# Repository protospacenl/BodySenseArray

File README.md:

# BodySenseArray
Body Sensor Array

## Data transfer
Data transfer between sensor units uses RS485. Use a RS485 to usb converter to send data over to the PC.

Serial settings:
 * Baudrate: 250000
 * 8n1
 * no flow control

## Sensor data format
Each packet starts with a `%` start token and ends with a CRC. Check the crc to verify data integrity. If crc is not valid the received packet should be discarded.

 * byte order: little endian
 * format: `%<id><temperature><acc_x><acc_y><acc_z><gyro_x><gyro_y><gyro_z><crc>`

field | type
--- | ---
% | uint8_t
id | uint8_t
temperature | uint16_t
acc_[xyz] | int16_t
gyro_[xyz] | int16_t
crc | uint8_t

## CRC
CRC algorithm used is the [Dalles iButton 8-bit CRC](https://www.microchip.com/webdoc/AVRLibcReferenceManual/group__util__crc_1ga37b2f691ebbd917e36e40b096f78d996.html).

Example C implementation  (taken from above link):
```C
uint8_t
_crc_ibutton_update(uint8_t crc, uint8_t data)
{
    uint8_t i;

    crc = crc ^ data;
    for (i = 0; i < 8; i++)
    {
        if (crc & 0x01)
            crc = (crc >> 1) ^ 0x8C;
        else
            crc >>= 1;
    }
    
    return crc;
}
```
or in python (see [examples](https://github.com/protospacenl/BodySenseArray/blob/90c5e3de4db39f0ca5cd2b3785d3c42a4cba6765/examples/serial_read/serial_read.py#L60) for usage)
```python
def compute_crc(data):
    crc = 0x00
    for c in data[:-1]:
        crc = crc ^ c
        for i in range(0, 8):
            if crc & 0x01:
                crc  = (crc >> 1) ^ 0x8c
            else:
                crc = crc >> 1
    return crc
```

## Conversions
For efficiency the sensor data is in its integer form and needs to be translated to real world values. 
See the [examples](https://github.com/protospacenl/BodySenseArray/tree/master/examples) for implementation details.

### Temperature
```python
def temperature_from_raw(t):
    return t * 0.00390625
```

### acceleration
Translation from the raw acceleration values to *g*:
`(float)in * 0.061 * (g >> 1) / 1000.0`  
where *in* is the raw 16-bit two's complement value and *g* is the sensitivity (currently 2).

Range for 2g:
 - min: -1.99848g
 - max: 1.99787g

Example:
```python
def acc_from_raw(in, g=2):
    return in * 0.061 * (g >> 1) / 1000.
 ```

### angular rate
Translation from the raw angular rate to *dps*:
`(float)in * 4.375 * (dps / 125) / 1000.0`
where *in* is the raw 16-bit two's complement value and *dps* is the sensitivity (currently 2000).

Range for 2000dps:
 - min: -2293.76 dps
 - max: 2293.69 dps

Example:
```python
def dps_from_raw(in, dps=2000):
  return in * 4.375 * (dps / 125) / 1000.
```

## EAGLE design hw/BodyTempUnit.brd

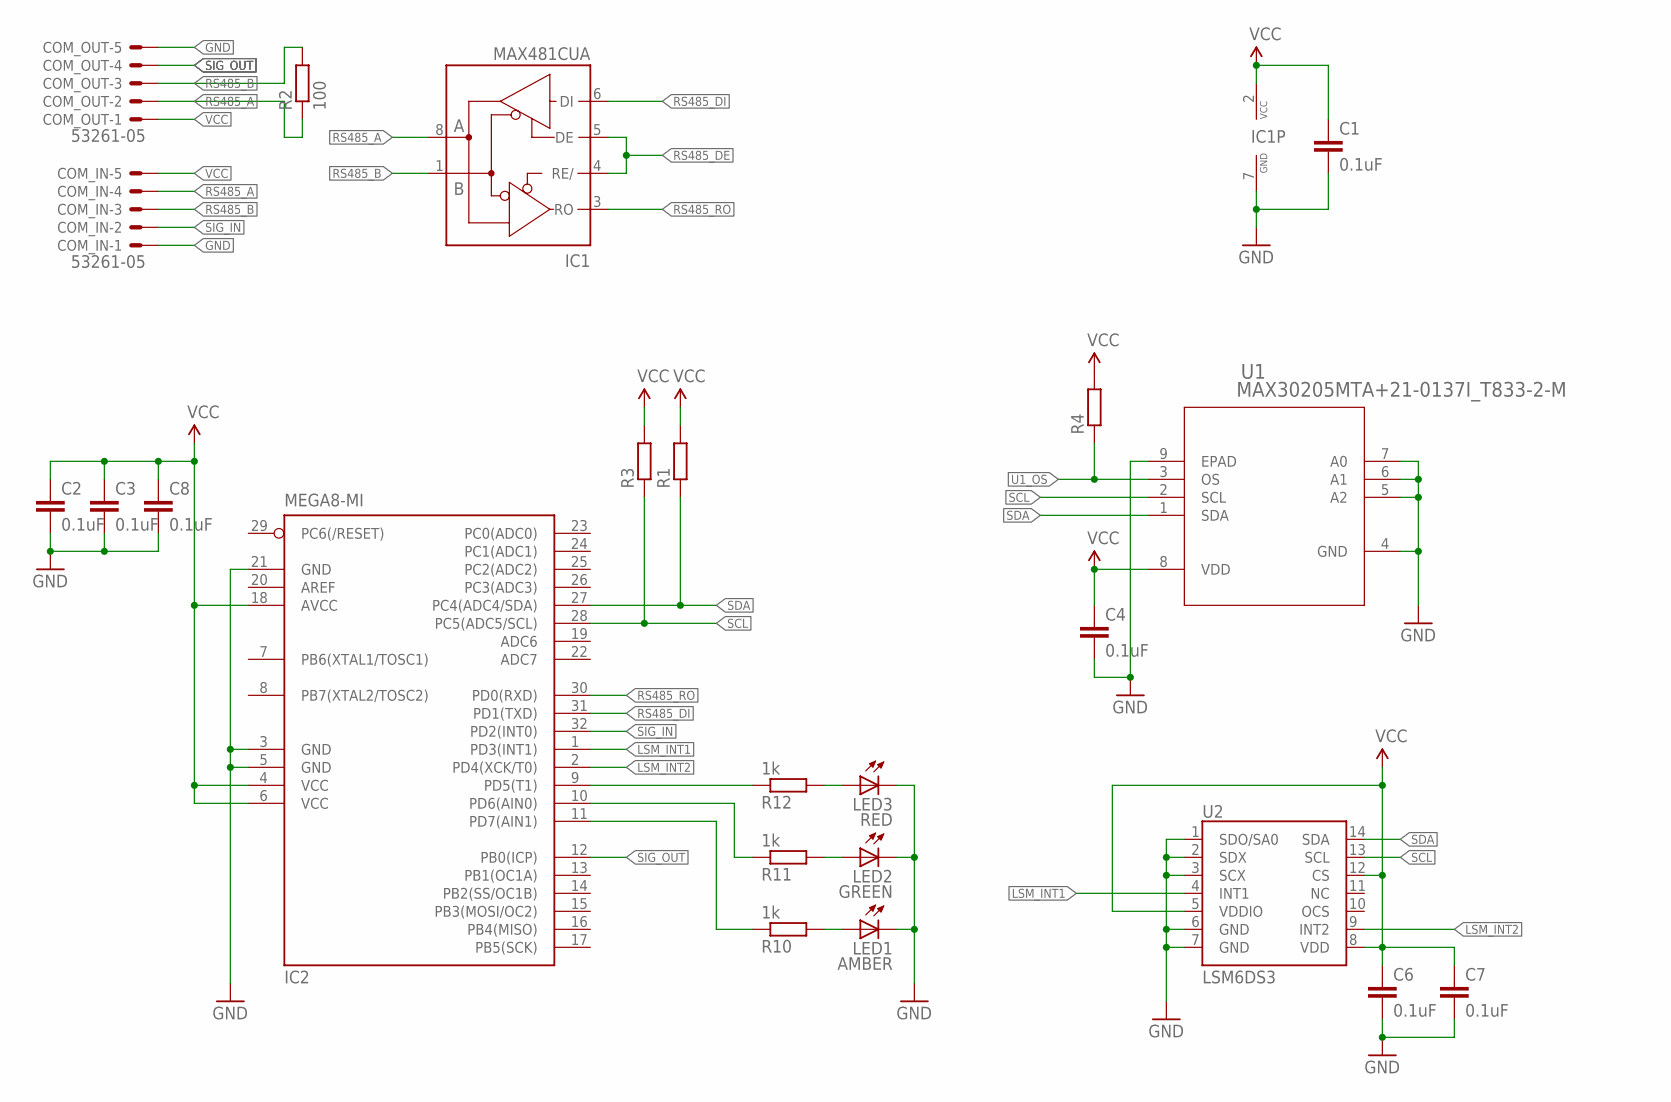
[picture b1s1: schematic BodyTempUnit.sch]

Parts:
C1, C2, C3, C4, C6, C7, C8: 0.1uF; C0603K
COM_IN: 53261-05
COM_OUT: 53261-05
IC1: MAX481CUA; UMAX8
IC2: MEGA8-MI; MLF32
LED1: AMBER; CHIPLED_0603
LED2: GREEN; CHIPLED_0603
LED3: RED; CHIPLED_0603
R1, R3, R4: R-EU_R0603; R0603
R2: 100; R0603
R10, R11, R12: 1k; R0603
U1: MAX30205MTA+21-0137I_T833-2-M; 21-0137I_T833-2-M
U2: LSM6DS3; LGA14L

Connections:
GND: C1.2, C2.2, C3.2, C4.2, C6.2, C7.2, C8.2, COM_IN.1, COM_OUT.5, IC1.7 (GND), IC2.3 (GND), IC2.5 (GND), IC2.21 (GND), LED1.C, LED2.C, LED3.C, U1.4 (GND), U1.5 (A2), U1.6 (A1), U1.7 (A0), U1.9 (EPAD), U2.1 (SDO/SA0), U2.2 (SDX), U2.3 (SCX), U2.6 (GND), U2.7 (GND)
LSM_INT1: IC2.1 (PD3(INT1)), U2.4 (INT1)
LSM_INT2: IC2.2 (PD4(XCK/T0)), U2.9 (INT2)
unnamed: IC2.10 (PD6(AIN0)), R11.1
unnamed: LED3.A, R12.2
unnamed: LED2.A, R11.2
unnamed: LED1.A, R10.2
unnamed: IC2.11 (PD7(AIN1)), R10.1
unnamed: IC2.9 (PD5(T1)), R12.1
RS485_A: COM_IN.4, COM_OUT.2, IC1.8 (A), R2.1
RS485_B: COM_IN.3, COM_OUT.3, IC1.1 (B), R2.2
RS485_DE: IC1.4 (RE/), IC1.5 (DE)
RS485_DI: IC1.6 (DI), IC2.31 (PD1(TXD))
RS485_RO: IC1.3 (RO), IC2.30 (PD0(RXD))
SCL: IC2.28 (PC5(ADC5/SCL)), R3.1, U1.2 (SCL), U2.13 (SCL)
SDA: IC2.27 (PC4(ADC4/SDA)), R1.1, U1.1 (SDA), U2.14 (SDA)
SIG_IN: COM_IN.2, IC2.32 (PD2(INT0))
SIG_OUT: COM_OUT.4, IC2.12 (PB0(ICP))
U1_OS: R4.1, U1.3 (OS)
VCC: C1.1, C2.1, C3.1, C4.1, C6.1, C7.1, C8.1, COM_IN.5, COM_OUT.1, IC1.2 (VCC), IC2.4 (VCC), IC2.6 (VCC), IC2.18 (AVCC), R1.2, R3.2, R4.2, U1.8 (VDD), U2.5 (VDDIO), U2.8 (VDD), U2.12 (CS)

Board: 4 copper layers, 23 parts (0 on the bottom side), 20 nets, no tracks yet.

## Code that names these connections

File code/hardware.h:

/* 
 * File:   hardware.h
 * Author: simon
 *
 * Created on July 4, 2019, 11:52 PM
 */

#ifndef HARDWARE_H
#define	HARDWARE_H

#ifdef	__cplusplus
extern "C" {
#endif

#define F_CPU           8000000UL
#define RS485_BAUDRATE  250000
    
#define LED_RED         PB1
#define LED_GREEN2      PB0
#define LED_GREEN1      PB2
#define SIG_IN          PD2
#define SIG_OUT         PD6
#define RS485_DE        PD5
    
#define MAX30205_ADDR   0x4F    /* temperature sensor */
#define LSM6DS3_ADDR    0x6A    /* IMU accel / gyro */

#ifdef	__cplusplus
}
#endif

#endif	/* HARDWARE_H */

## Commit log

2019-06-04 Moved to hw folder
2019-06-06 Removed old files
2019-06-06 gitignore for eagle & kicad
2019-06-06 KiCad body sense array
2019-06-07 Few fixes in schematic
    * Power flags to gnd and vcc to avoid erc warning
    * Checked connections (OK)
    * Flaged nc connections accordingly to avoid erc warnings
    * Removed project specific symbol libs from global table
    * Connected RS485_DE to PD5
    * Moved LED3 from PD5 -> PD7
2019-06-07 Added PS worksheet
2019-06-07 GND pour added to mlf footprint
2019-06-07 switched regulator with RS485
2019-06-07 Added project file
2019-06-08 some rerouting
2019-06-08 Reroute ISP
2019-06-10 Routing mostly done
2019-06-10 Ready for final check
2019-06-11 All routed, final check pending
2019-06-13 version sent to production
2019-07-06 Added .gitignore entries for mplabX
2019-07-06 initial code commit
2019-08-08 Working gyro and acc
2019-08-10 Binary output
2019-08-10 Added jupiter-notebook example
2019-10-10 added pyvis wip example
2019-10-10 Increased accel sensitivity to 2g
2019-10-10 Placed ascii output under DEBUG define
2019-10-10 Realtime signal demo
2019-10-10 Moved bare serial read to own dir
2019-10-10 increased sensitivity to 2g for accelerometer
2019-10-10 Added pip requirements files
2019-10-10 Some nice formatting
